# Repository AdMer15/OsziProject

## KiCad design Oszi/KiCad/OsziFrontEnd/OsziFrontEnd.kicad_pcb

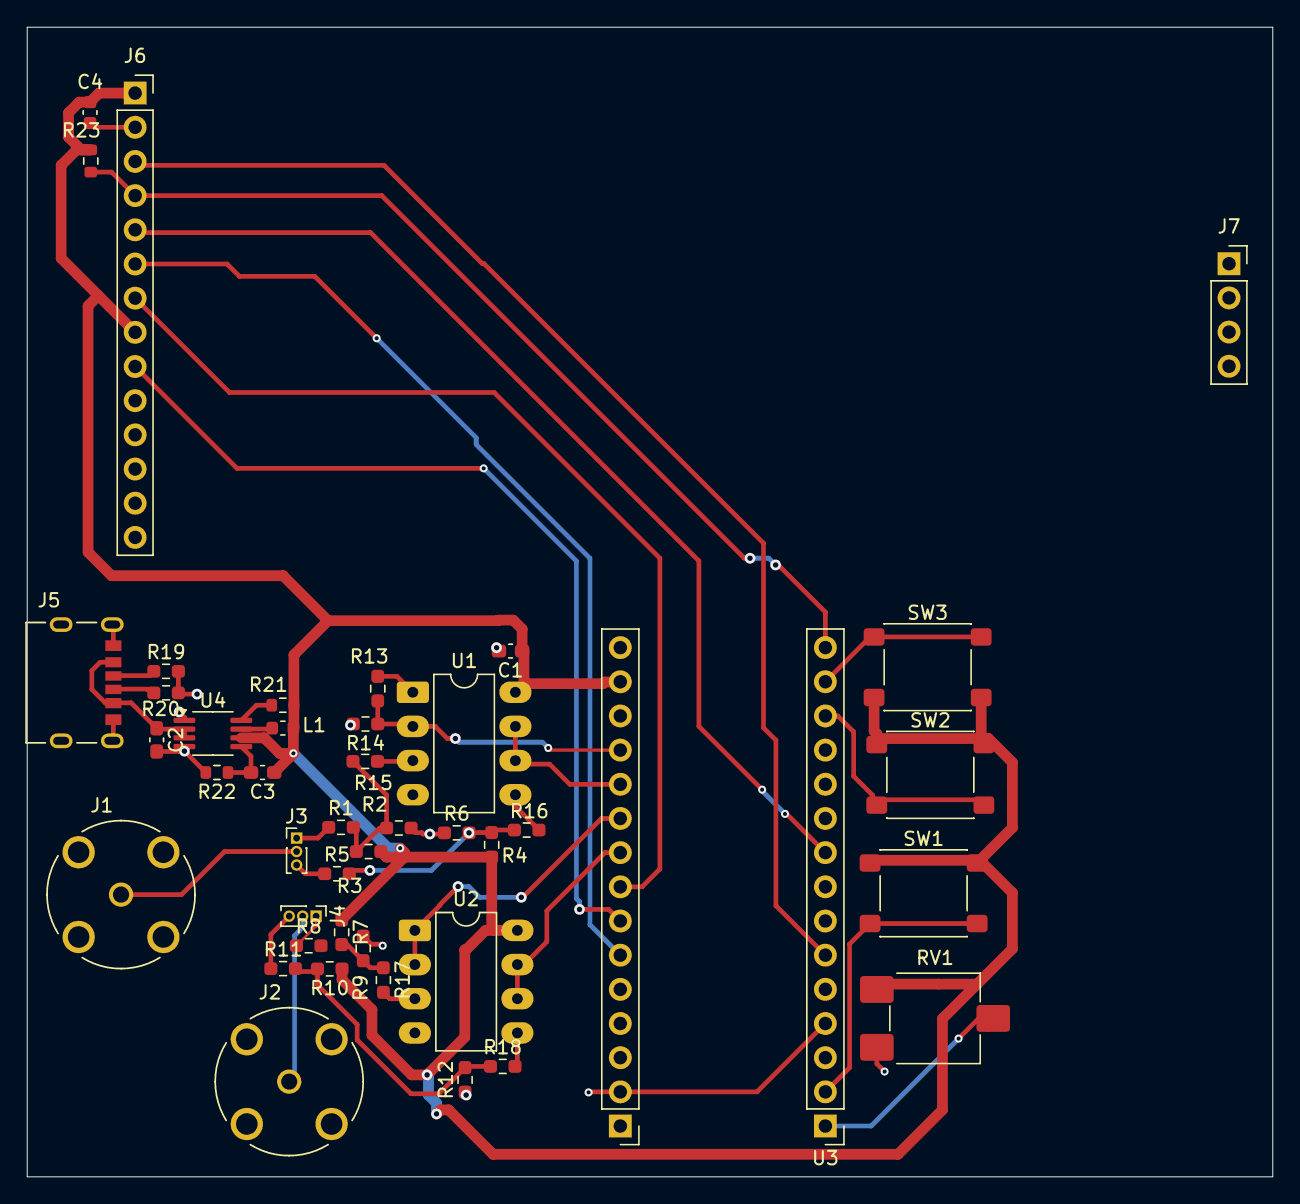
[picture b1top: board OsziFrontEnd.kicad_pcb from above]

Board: 2 copper layers, 92.6 x 85.4 mm, 43 parts (0 on the bottom side), 38 nets.

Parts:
C1: 12pF; C_0603_1608Metric_Pad1.08x0.95mm_HandSolder
C2: 10u; C_0603_1608Metric_Pad1.08x0.95mm_HandSolder
C3: 22u; C_0603_1608Metric_Pad1.08x0.95mm_HandSolder
C4: 12p; C_0603_1608Metric
J1, J2: Conn_Coaxial; LINX_CONBNC001
J3, J4: Conn_01x03_Pin; PinHeader_1x03_P1.00mm_Vertical
J5: USB_C_Receptacle_PowerOnly_6P; SAMESKY_UJC-H-G-SMT-2-P6-TR
J6: Conn_01x14_Socket; PinSocket_1x14_P2.54mm_Vertical
J7: Conn_01x04_Socket; PinSocket_1x04_P2.54mm_Vertical
L1: 2.2u; L_0603_1608Metric
R1: 220k; R_0603_1608Metric_Pad0.98x0.95mm_HandSolder
R2: 430k; R_0603_1608Metric_Pad0.98x0.95mm_HandSolder
R3, R5, R11: 750k; R_0603_1608Metric_Pad0.98x0.95mm_HandSolder
R4, R10: 240k; R_0603_1608Metric_Pad0.98x0.95mm_HandSolder
R6, R12: 370k; R_0603_1608Metric_Pad0.98x0.95mm_HandSolder
R7: 82k; R_0603_1608Metric_Pad0.98x0.95mm_HandSolder
R8: 910k; R_0603_1608Metric_Pad0.98x0.95mm_HandSolder
R9: 91k; R_0603_1608Metric_Pad0.98x0.95mm_HandSolder
R13: 200k; R_0603_1608Metric_Pad0.98x0.95mm_HandSolder
R14: 100k; R_0603_1608Metric_Pad0.98x0.95mm_HandSolder
R15, R16, R17, R18: 100; R_0603_1608Metric_Pad0.98x0.95mm_HandSolder
R19, R20: 5k2; R_0603_1608Metric_Pad0.98x0.95mm_HandSolder
R21: 330k; R_0603_1608Metric
R22: 100k; R_0603_1608Metric
R23: 10k; R_0603_1608Metric
RV1: R_Potentiometer; Potentiometer_ACP_CA6-VSMD_Vertical
SW1, SW2, SW3: SW_Push; SW_SPST_PTS645Sx43SMTR92
U1, U2: MCP6002-xP; DIP-8_W7.62mm_LongPads
U3: NUCLEO-L432KC; NUCLEO-L432KC_Module
U4: TPS62160DGK; MSOP-8_3x3mm_P0.65mm

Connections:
3V3: C1.1, C3.1, C4.2, J6.1, J6.8, L1.2, R3.1, R4.1, R7.1, R10.1, R21.1, R23.2, RV1.3, SW1.1, SW2.1, SW3.2, U1.8 (V+), U2.8 (V+), U3.CN4_14 (+3V3), U4.6 (VOS)
/AnalogesFrontEnd/ADC_CH1_1V: R13.2, R14.1, U1.2 (-), U3.CN4_12 (PA0)
/AnalogesFrontEnd/ADC_CH1_10V: U1.6 (-), U1.7, U3.CN4_11 (PA1)
/AnalogesFrontEnd/ADC_CH2_10V: U2.6 (-), U2.7, U3.CN4_9 (PA4)
/AnalogesFrontEnd/ADC_CH2_36V: U2.1, U2.2 (-), U3.CN4_10 (PA3)
/AnalogesFrontEnd/CoaxCH1: J1.1 (In), J3.2
/AnalogesFrontEnd/CoaxCH2: J2.1 (In), J4.2
/AnalogesFrontEnd/Vin-1;1CH1: J3.1, R1.1
/AnalogesFrontEnd/Vin-10;10CH1: J3.3, R5.1
/AnalogesFrontEnd/Vin-10;10CH2: J4.3, R11.1
/AnalogesFrontEnd/Vin-36;36CH2: J4.1, R8.1
/AnalogesFrontEnd/Vout-1;1CH1: R1.2, R2.2, R3.2, R15.1
/AnalogesFrontEnd/Vout-10;10CH1: R4.2, R5.2, R6.2, R16.1
/AnalogesFrontEnd/Vout-10;10CH2: R10.2, R11.2, R12.2, R18.1
/AnalogesFrontEnd/Vout-36;36CH2: R7.2, R8.2, R9.2, R17.1
/Display/DCS: J6.3, U3.CN3_6 (PB0)
/Display/DD/C: J6.5, U3.CN3_9 (PB1)
/Display/DMISO: J6.9, U3.CN4_7 (PA6)
/Display/DMOSI: J6.6, U3.CN4_6 (PA7)
/Display/DRs: J6.4, R23.1, U3.CN3_15 (PB4)
/Display/DSCK: J6.7, U3.CN4_8 (PA5)
/powerSupplie/USB-cOut: C2.1, J5.A9 (VBUS), J5.B9 (VBUS), U4.2 (VIN), U4.3 (EN)
GND: C1.2, C2.2, C4.1, J1.2 (Ext), J2.2 (Ext), J5.A12 (GND), J5.B12 (GND), J5.S1 (SHIELD), J6.2, R2.1, R6.1, R9.1, R12.1, R14.2, R19.2, R20.2, R22.2, RV1.1, U1.4 (V-), U2.4 (V-), U4.1 (PGND), U4.4 (AGND)
GNDD: U3.CN3_4 (GND_CN3), U3.CN4_2 (GND_CN4)
unnamed: J5.A5 (CC1), R19.1
unnamed: J5.B5 (CC2), R20.1
unnamed: R13.1, U1.1
unnamed: R15.2, U1.3 (+)
unnamed: R16.2, U1.5 (+)
unnamed: R17.2, U2.3 (+)
unnamed: R18.2, U2.5 (+)
unnamed: RV1.2, U3.CN3_1 (PA9)
unnamed: SW1.2, U3.CN3_2 (PA10)
unnamed: SW2.2, U3.CN3_13 (PA11)
unnamed: SW3.1, U3.CN3_14 (PB5)
unnamed: C3.2, R22.1, U4.5 (FB)
unnamed: R21.2, U4.8 (PG)
unnamed: L1.1, U4.7 (SW)

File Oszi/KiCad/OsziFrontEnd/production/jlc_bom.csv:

Designator,Footprint,Quantity,Value,LCSC Part #
C1,0603,1,12pF,
C2,0603,1,10u,
C3,0603,1,22u,
C4,0603,1,12p,
"CH SELECT, MODE SELECT, RUN / STOP",SW_SPST_PTS645Sx43SMTR92,3,SW_Push,
"J1, J2",LINX_CONBNC001,2,Conn_Coaxial,
"J3, J4",PinHeader_1x03_P1.00mm_Vertical,2,Conn_01x03_Pin,
J5,SAMESKY_UJC-H-G-SMT-2-P6-TR,1,USB_C_Receptacle_PowerOnly_6P,
L1,0603,1,2.2u,
R1,0603,1,220k,
"R10, R4",0603,2,240k,
"R11, R3, R5",0603,3,750k,
"R12, R6",0603,2,370k,
R13,0603,1,200k,
"R14, R22",0603,2,100k,
"R15, R16, R17, R18",0603,4,100,
"R19, R20",0603,2,5k2,
R2,0603,1,430k,
R21,0603,1,330k,
R23,0603,1,10k,
R7,0603,1,82k,
R8,0603,1,910k,
R9,0603,1,91k,
TRIMM,Potentiometer_ACP_CA6-VSMD_Vertical,1,R_Potentiometer,
"U1, U2",DIP-8_W7.62mm_LongPads,2,MCP6002-xP,
U3,NUCLEO-L432KC_Module,1,NUCLEO-L432KC,
U4,MSOP-8_3x3mm_P0.65mm,1,TPS62160DGK,
U6,CR2013-MI2120,1,CR2013-MI2120,

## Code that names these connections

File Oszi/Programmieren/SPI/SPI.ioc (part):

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Mcu.Name=STM32L432K(B-C)Ux
Mcu.Package=UFQFPN32
Mcu.UserName=STM32L432KCUx
PA0.GPIOParameters=GPIO_Label
PA0.GPIO_Label=ADC_CH1_1V
PA0.Signal=ADCx_IN5
PA1.GPIOParameters=GPIO_Label
PA1.GPIO_Label=ADC_CH1_10V
PA1.Signal=ADCx_IN6
PA13\ (JTMS-SWDIO).GPIOParameters=GPIO_Label
PA13\ (JTMS-SWDIO).GPIO_Label=SWDIO
PA13\ (JTMS-SWDIO).Mode=Serial_Wire
PA13\ (JTMS-SWDIO).Signal=SYS_JTMS-SWDIO
PA14\ (JTCK-SWCLK).GPIOParameters=GPIO_Label
PA14\ (JTCK-SWCLK).GPIO_Label=SWCLK
PA14\ (JTCK-SWCLK).Mode=Serial_Wire
PA14\ (JTCK-SWCLK).Signal=SYS_JTCK-SWCLK
PA15\ (JTDI).GPIOParameters=GPIO_Label
PA15\ (JTDI).GPIO_Label=VCP_RX
PA15\ (JTDI).Mode=Asynchronous
PA15\ (JTDI).Signal=USART2_RX
PA2.GPIOParameters=GPIO_Label
PA2.GPIO_Label=VCP_TX
PA2.Mode=Asynchronous
PA2.Signal=USART2_TX
PA3.GPIOParameters=GPIO_Label
PA3.GPIO_Label=ADC_CH2_36V
PA3.Signal=ADCx_IN8
PA4.GPIOParameters=GPIO_Label
PA4.GPIO_Label=ADC_CH2_10V
PA4.Signal=ADCx_IN9
PA5.Mode=TX_Only_Simplex_Unidirect_Master
PA5.Signal=SPI1_SCK
PA6.Signal=SPI1_MISO
PA7.Mode=TX_Only_Simplex_Unidirect_Master
PA7.Signal=SPI1_MOSI
PA8.Signal=S_TIM1_CH1
PB0.GPIOParameters=GPIO_Label
PB0.GPIO_Label=CS
PB0.Signal=GPIO_Output
PB1.GPIOParameters=GPIO_Label
PB1.GPIO_Label=DC
PB1.Signal=GPIO_Output
PB4\ (NJTRST).GPIOParameters=GPIO_Label
PB4\ (NJTRST).GPIO_Label=DRS
PB4\ (NJTRST).Signal=GPIO_Output
PC14-OSC32_IN\ (PC14).Mode=LSE-External-Oscillator
PC14-OSC32_IN\ (PC14).Signal=RCC_OSC32_IN
PC15-OSC32_OUT\ (PC15).Mode=LSE-External-Oscillator
PC15-OSC32_OUT\ (PC15).Signal=RCC_OSC32_OUT
RCC.HSE_VALUE=8000000
RCC.SYSCLKFreq_VALUE=80000000
RCC.SYSCLKSource=RCC_SYSCLKSOURCE_PLLCLK
board=NUCLEO-L432KC
boardIOC=true

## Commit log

2025-09-19 init commit
2025-10-18 added usb-c and front end
2025-10-24 startet coding and configure .ios
2025-10-29 added display in KiCad
2025-10-29 added buttons 4 display
2025-10-31 finished layout
2025-11-28 added CubeIDE project
2025-11-28 finsihed layout
2025-11-28 fixed spacing on pcb
2025-12-05 jetzt git
2025-12-05 added LaTeX documentation
2025-12-05 restructored documentation folder
2025-12-05 removed redundend files and folders
2025-12-05 working SPI clock in SPI
2025-12-05 cube project SPI moved and working
2025-12-05 ili9341 fillscreen works
2026-01-18 drawing grid with test signal but still wrong rotaton
2026-01-18 rotaded 90degress
2026-01-20 delletd unasasarie folder
2026-01-22 ADC multirange measurement working
2026-01-29 ennabeld dma on 4ADC in ios
2026-01-30 adc working with dma giving right values 2 cmd
2026-01-30 adc working everything seperatet into .c and .h files
2026-01-30 adc gets plottet on screen but locks bad
2026-02-05 added scalling partlie works
